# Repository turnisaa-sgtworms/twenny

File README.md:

twenny, 20 key wireless split.

features: 
 - diodeless
 - reversible
 - throughole soldered xiao
 - cheap! fits jlcpcb's 2 dollar pcb requirements... good even for the tariffs we're getting right now in the US.
 - two 3dp case options, one with a cut acrylic top
 - easy (but mildly jank, fine as long as you follow instructions) assembly. just solder on a xiao and switches and you're good to go!

**IF YOU DO NOT READ THE BUILD GUIDE THIS THING WILL PROBABLY EXPLODE!!!!! READ IT!!!!!**

# bill of materials

2x - twenny pcb

2x - seeed xiao nrf52840 dev boards

20x - choc v1 switches of choice

20x - choc v1 keycaps of choice

2x - adafruit lipo 100mAh battery - product id 1570 (both cases are designed to use this battery)

2x - female jst connector

**For the new case:**

1x (of each) - 3d printed case parts

*optional based on your bottom case choice*: 12x - 2mm thick, 3.5mm outer diameter m.2 heat inserts

*also optional*: 12x - 2mm thick, 3.5mm outer diameter m.2 heat inserts

12x - 5mm m.2 screws

**For the old case:**

1x (of each) - 3d printed case parts

2x - cut acrylic, somewhere between 1 and 2 mm thick

12x - 2mm thick, 3.5mm outer diameter m.2 heat inserts

8x - 5mm m.2 screws

4x - 14mm m.2 screws

# quick guide, INCOMPLETE probably, will add pics eventually:

**1 THE HARD PART:**

       you may want to do this after part two, read all the steps then decide for yourself 
       which direction you want to take.
  
       you will need to solder the female jst connectors to the battery pads on the bottom 
       of each xiao. NOTE! that many jst connectors may be backwards, so if the wires do not 
       match the wires on your battery when plugged in you should be able to unclip them
       and swap them so that they do.
  
       mock up the final build so you can trim your jst connectors to fit as well as possible. 
       i probably could have cut mine shorter, but that's fine.
  
       solder em on! the pads are small and close together so be sure they will not short, 
       and be sure they will not block the pin headers!
  
**2 THE JANK PART - SUPER IMPORTANT!!:**

       clip the pin headers included with your xiao so you 
       have the following lengths (for each board!):
  
             1x - 4 pins long
    
             1x - 5 pins long
    
             5x - 1 pin long
    
       remove the plastic bits from 3 of the 1 pin bits, **SAVE THE PLASTIC!** 
       the metal pin piece for these three can be tossed.
  
       solder the headers on so that:
  
             on the left side, from top to bottom you have 
             1 pin, 1 space, then 5 pins soldered.
    
             on the right side, from top to bottom you have 
             1 space, 1 pin, 1 more space, and then 4 pins soldered.
    
       ADD THE EXTRA PLASTIC TO THE TOP AND BOTTOM PINS ON THE LEFT, 
       AND THE MIDDLE PIN ON THE RIGHT! THE EXTRA HEIGHT IS NECESSARY!
  
       ensure all the pins are straight by mocking it all together 
       with the pcb when you solder the pins to the dev board.
  
**3 THE EASY PART:**

       once you have the jst connector and pin headers soldered 
       to the dev board, solder it onto the pcb!
       note that 3 pins will be UNPOPULATED! the board is completely 
       reversible as long as you follow the steps above.
  
       now, feel free to solder your choc switches of choice onto the board.
  
**4 THE HOT PART (IS THIS GAG STILL FUNNY?):**

       set your soldering iron to just above the melting temp of
       whatever you printed your case in, i think i did about 10C over.
  
       choose a tip that you can poke into the heat inserts and it 
       will kind of pick them up, without protruding too far through them.
  
       use pliers or something along those lines to put each heat insert 
       onto the soldering iron, then push them into each of the heat insert 
       holes till they are flush. you may want a damp paper towel to cool 
       and flatten the plastic once they are placed 
       (or just burn your thumb a little if youre kinda dumb like me)
  
       there should be 4 heat insert holes on the top face of 
       each half (two on each piece) and 2 on the inside of
       the bottom part of each half.
    
**5 THE EASY PART AGAIN:**

       screw each case half together with 14mm m.2 screws through 
       the top part of each half into the heat inserts on the inside of 
       the bottom part of each half. leave these loose till later.
  
       install your battery in the gap in each case, 
       install your pcb on top of it.
  
       slip the acrylic piece on top, and screw the 5mm 
       m.2 screws into the heat inserts through the holes in it. 
       leave em loose till you have them all started, then 
       tighten the bottom screws, then tighten the top screws down evenly.
  
**6 THE FIRM PART:**

       flash some firmware on that bad boy!
  
       note: you will need a bind for SOFT OFF. this keeb 
       shas no physical off switch, but soft off works great.

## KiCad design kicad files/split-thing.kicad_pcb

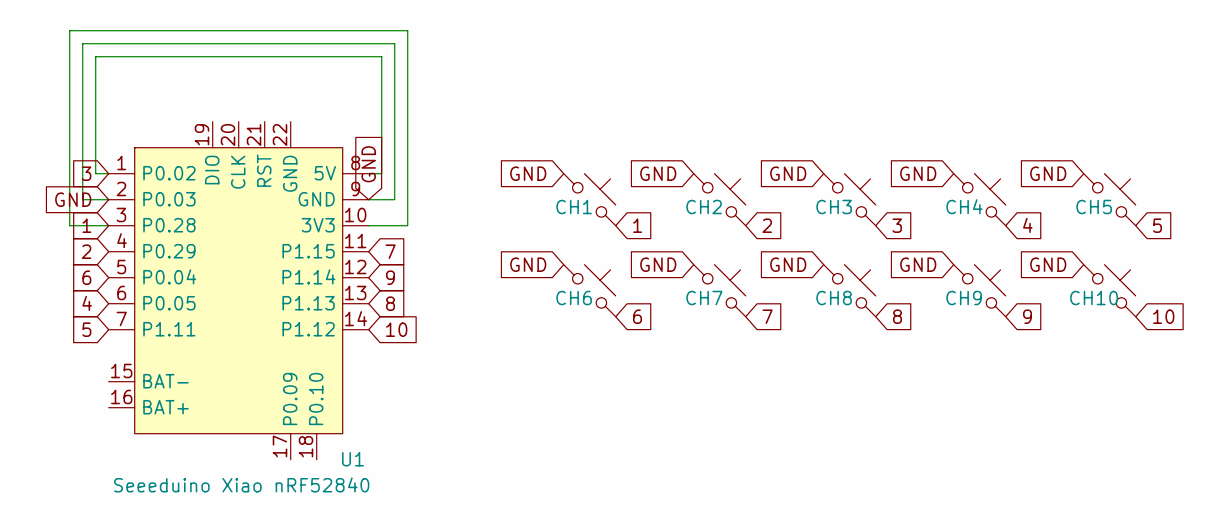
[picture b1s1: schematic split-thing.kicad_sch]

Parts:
CH1, CH2, CH3, CH4, CH5, CH6, CH7, CH8, CH9, CH10: choc_v1_SW_solder; SW_choc_Reversible_1u
U1: Seeeduino Xiao nRF52840; Xiao_nRF52840_AH_Pogo_1

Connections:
1: CH1.2, U1.3 (P0.28), U1.10 (3V3)
2: CH2.2, U1.4 (P0.29)
3: CH3.2, U1.1 (P0.02), U1.8 (5V)
4: CH4.2, U1.6 (P0.05)
5: CH5.2, U1.7 (P1.11)
6: CH6.2, U1.5 (P0.04)
7: CH7.2, U1.11 (P1.15)
8: CH8.2, U1.13 (P1.13)
9: CH9.2, U1.12 (P1.14)
10: CH10.2, U1.14 (P1.12)
GND: CH1.1, CH2.1, CH3.1, CH4.1, CH5.1, CH6.1, CH7.1, CH8.1, CH9.1, CH10.1, U1.2 (P0.03), U1.9 (GND)

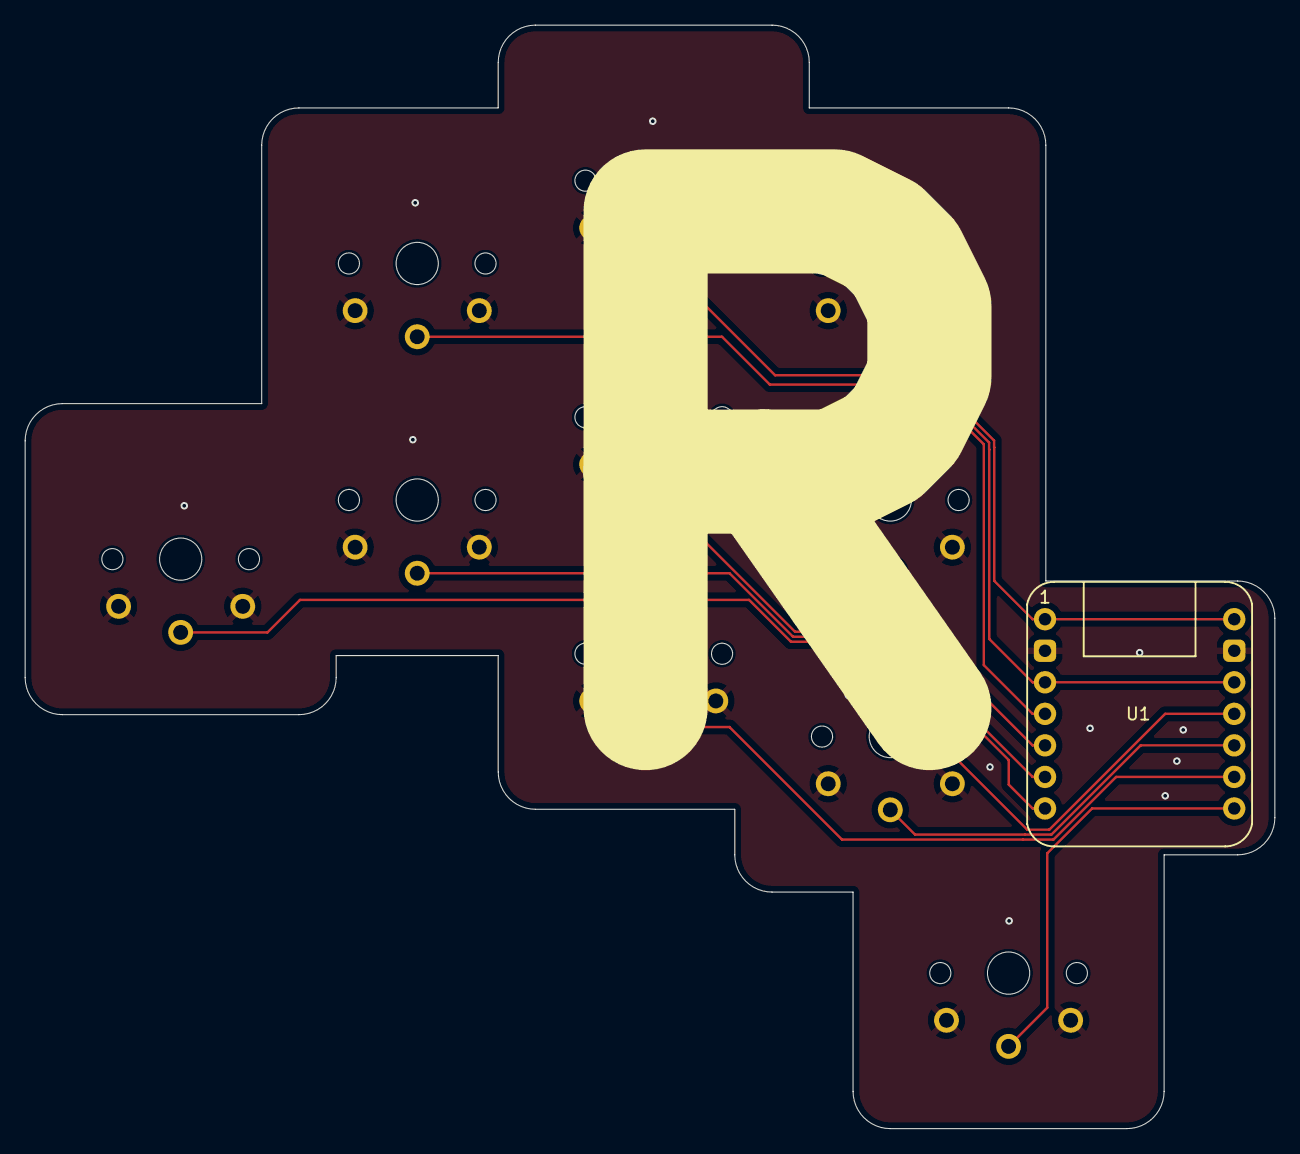
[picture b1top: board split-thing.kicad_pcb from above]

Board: 2 copper layers, 100.6 x 88.9 mm, 11 parts (0 on the bottom side), 11 nets.

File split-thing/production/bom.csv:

Designator,Footprint,Quantity,Value,LCSC Part #
"CH1, CH10, CH2, CH3, CH4, CH5, CH6, CH7, CH8, CH9",SW_choc_Reversible_1u,10,choc_v1_SW_solder,

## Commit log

2025-04-07 swag device
2025-04-10 added case files
2025-05-28 added diy files
2025-06-26 added firmware
2025-07-23 added new case files
